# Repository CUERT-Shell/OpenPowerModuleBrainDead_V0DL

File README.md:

# OpenPowerModule

Kicad Design 
You can view on https://kicanvas.org (for non kicad users)

Minimal BLDC drive hardware (without microcontroller)

### The hardware 
* 3phase H-bridge and all its related circuitry (MGD , Snubber , decoupling , etc)
* Hall Sensor Conditioning Circuits
* IDC-2x15 Connector to be interfaced with a controller/MCU
* 12V-->5V buck converter , 3.3V LDO

### Repo Structure
* Main directory : design files
* Production directory : Gerbers and Bom
* LIB : Project Components library
* Doc : Design Reference , guide , step file , etc...

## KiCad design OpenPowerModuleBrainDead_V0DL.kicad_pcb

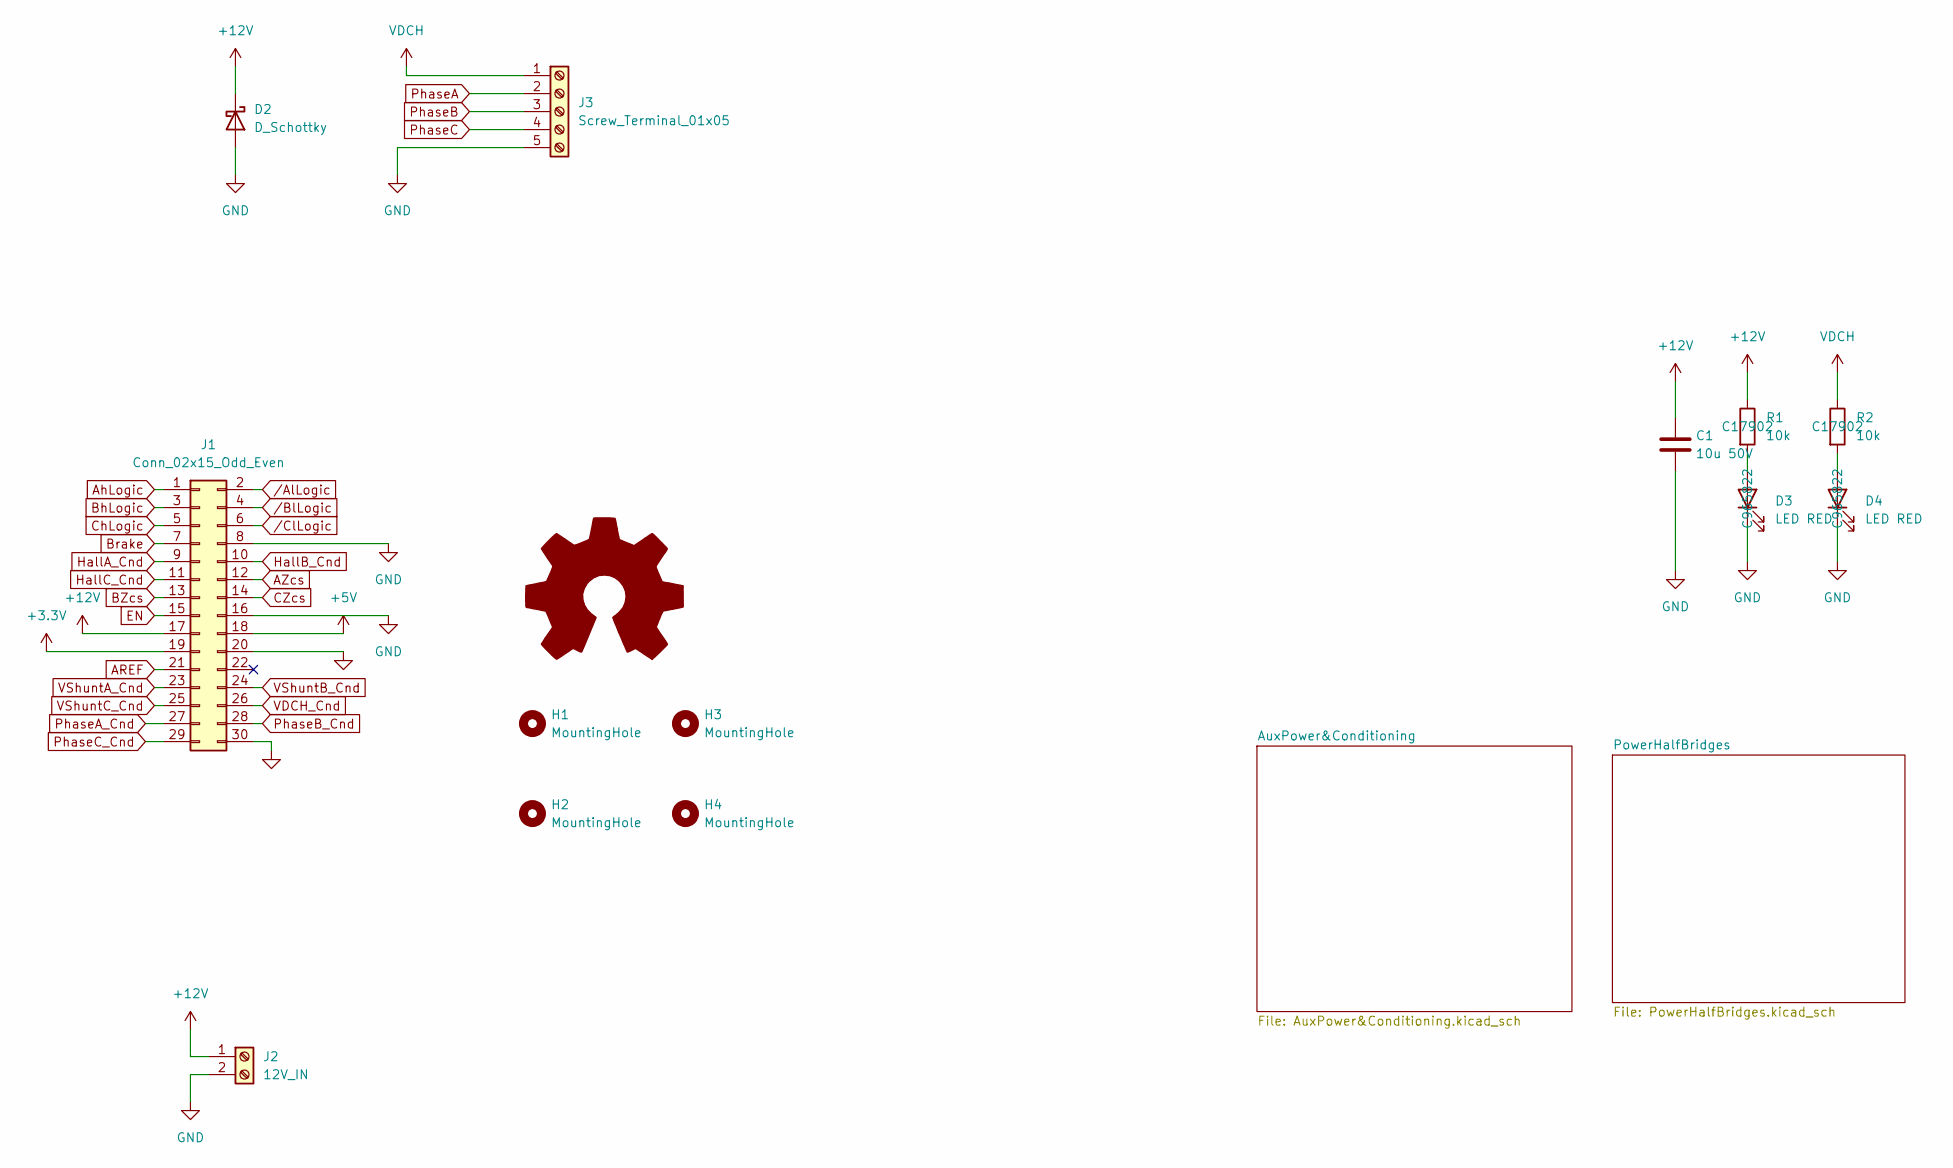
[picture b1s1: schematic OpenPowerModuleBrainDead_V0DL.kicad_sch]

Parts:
C1: 10u 50V; C_1206_3216Metric; LCSC Part C13585
D2: D_Schottky; D_SMC-RM10_Universal_Handsoldering
D3, D4: LED RED; LED_1206_3216Metric_Pad1.42x1.75mm_HandSolder; LCSC Part C965822
H1, H2, H3, H4: MountingHole; MountingHole_3.2mm_M3_DIN965
H5: Logo_Open_Hardware_Large; MadeWithKicad
J1: Conn_02x15_Odd_Even; IDC-Header_2x15_P2.54mm_Vertical
J2: 12V_IN; TerminalBlock_Phoenix_PT-1,5-2-3.5-H_1x02_P3.50mm_Horizontal
J3: Screw_Terminal_01x05; PowerConn_01x05_P20
R1, R2: 10k; R_1206_3216Metric; LCSC Part C17902

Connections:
+3.3V: J1.19; also elsewhere on the board
+5V: J1.18; also elsewhere on the board
+12V: C1.1, D2.1 (K), J1.17, J2.1, R1.1; also elsewhere on the board
AREF: J1.21
AZcs: J1.12
AhLogic: J1.1; also elsewhere on the board
BZcs: J1.13
BhLogic: J1.3; also elsewhere on the board
Brake: J1.7
CZcs: J1.14
ChLogic: J1.5; also elsewhere on the board
EN: J1.15
GND: C1.2, D2.2 (A), D3.1 (K), D4.1 (K), J1.8, J1.16, J1.20, J1.30, J2.2, J3.5; also elsewhere on the board
HallA_Cnd: J1.9; also elsewhere on the board
HallB_Cnd: J1.10; also elsewhere on the board
HallC_Cnd: J1.11; also elsewhere on the board
unnamed: D3.2 (A), R1.2
unnamed: D4.2 (A), R2.2
PhaseA: J3.2; also elsewhere on the board
PhaseA_Cnd: J1.27
PhaseB: J3.3; also elsewhere on the board
PhaseB_Cnd: J1.28
PhaseC: J3.4; also elsewhere on the board
PhaseC_Cnd: J1.29
VDCH: J3.1, R2.1; also elsewhere on the board
VDCH_Cnd: J1.26
VShuntA_Cnd: J1.23
VShuntB_Cnd: J1.24
VShuntC_Cnd: J1.25
/AlLogic: J1.2; also elsewhere on the board
/BlLogic: J1.4; also elsewhere on the board
/ClLogic: J1.6; also elsewhere on the board

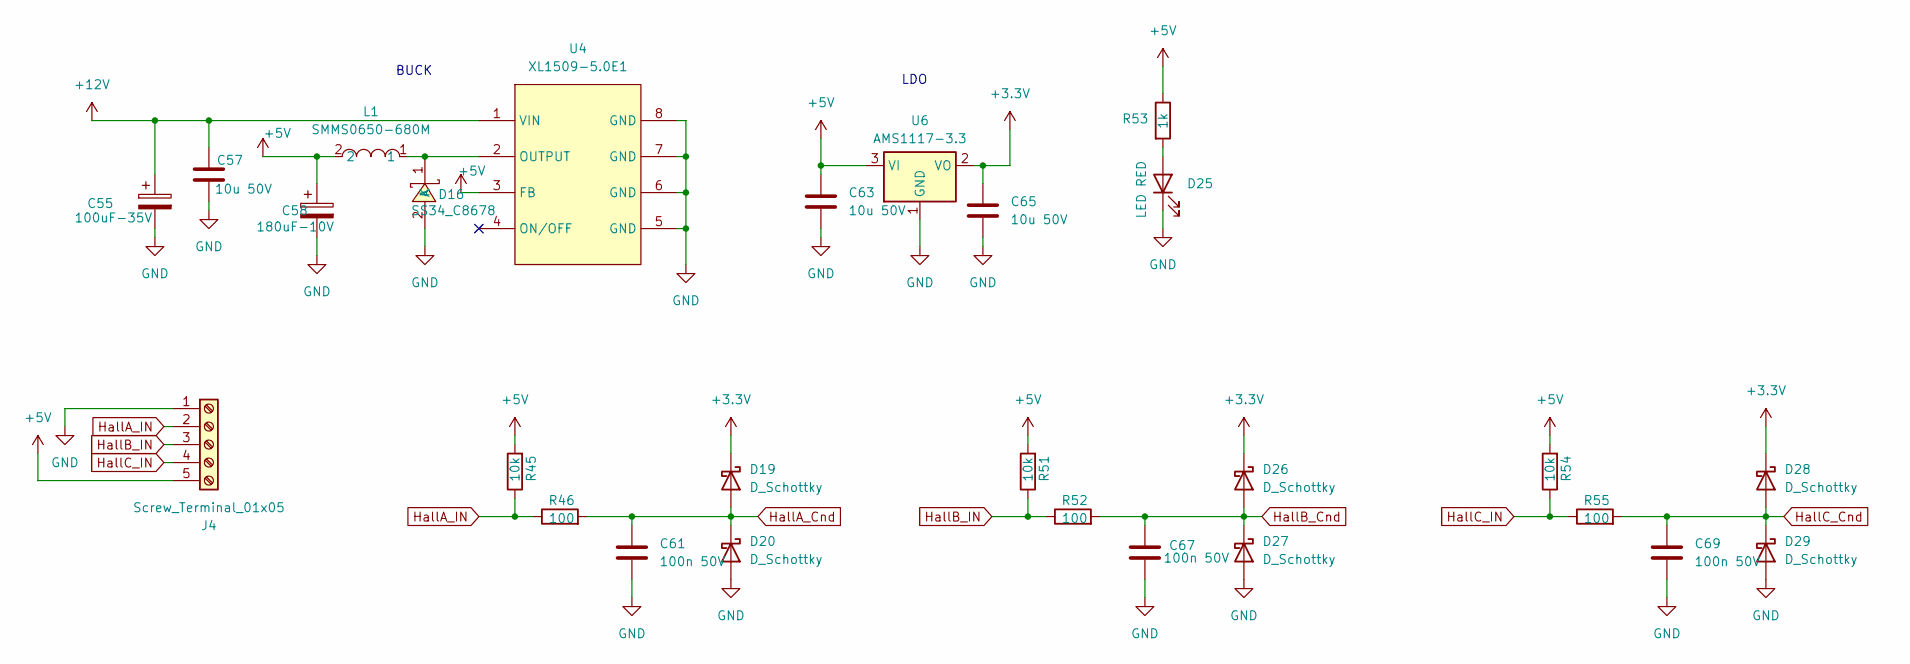
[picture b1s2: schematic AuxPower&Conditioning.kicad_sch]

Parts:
C55: 100uF-35V; CP_Radial_D6.3mm_P2.50mm
C57, C63, C65: 10u 50V; C_1206_3216Metric; LCSC Part C13585
C58: 180uF-10V; CP_Radial_D6.3mm_P2.50mm
C61, C67, C69: 100n 50V; C_1206_3216Metric; LCSC Part C24497
D16: SS34_C8678; SMA_L4.3-W2.6-LS5.2-RD; LCSC Part C8678
D19, D20, D26, D27, D28, D29: D_Schottky; D_SOD-123; LCSC Part C181204
D25: LED RED; LED_1206_3216Metric_Pad1.42x1.75mm_HandSolder; LCSC Part C965822
J4: Screw_Terminal_01x05; CONN-TH_5P-P3.50_DORABO_DB125-3.5-5P-GN-S
L1: SMMS0650-680M; IND-SMD_L7.1-W6.6_H5.0; LCSC Part C2894721
R45, R51, R54: 10k; R_1206_3216Metric; LCSC Part C17902
R46, R52, R55: 100; R_1206_3216Metric; LCSC Part C113307
R53: 1k; R_1206_3216Metric; LCSC Part C2907440
U4: XL1509-5.0E1; SOIC-8_L5.0-W4.0-P1.27-LS6.0-BL; LCSC Part C61063
U6: AMS1117-3.3; SOT-223-3_TabPin2; LCSC Part C347222

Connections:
+3.3V: C65.1, D19.1 (K), D26.1 (K), D28.1 (K), U6.2 (VO); also elsewhere on the board
+5V: C58.1, C63.1, J4.5, L1.2, R45.2, R51.2, R53.1, R54.2, U4.3 (FB), U6.3 (VI); also elsewhere on the board
+12V: C55.1, C57.1, U4.1 (VIN); also elsewhere on the board
GND: C55.2, C57.2, C58.2, C61.2, C63.2, C65.2, C67.2, C69.2, D16.2 (A), D20.2 (A), D25.1 (K), D27.2 (A), D29.2 (A), J4.1, U4.5 (GND), U4.6 (GND), U4.7 (GND), U4.8 (GND), U6.1 (GND); also elsewhere on the board
HallA_Cnd: C61.1, D19.2 (A), D20.1 (K), R46.2; also elsewhere on the board
HallA_IN: J4.2, R45.1, R46.1
HallB_Cnd: C67.1, D26.2 (A), D27.1 (K), R52.2; also elsewhere on the board
HallB_IN: J4.3, R51.1, R52.1
HallC_Cnd: C69.1, D28.2 (A), D29.1 (K), R55.2; also elsewhere on the board
HallC_IN: J4.4, R54.1, R55.1
unnamed: D16.1 (K), L1.1, U4.2 (OUTPUT)
unnamed: D25.2 (A), R53.2

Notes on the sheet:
LDO
BUCK

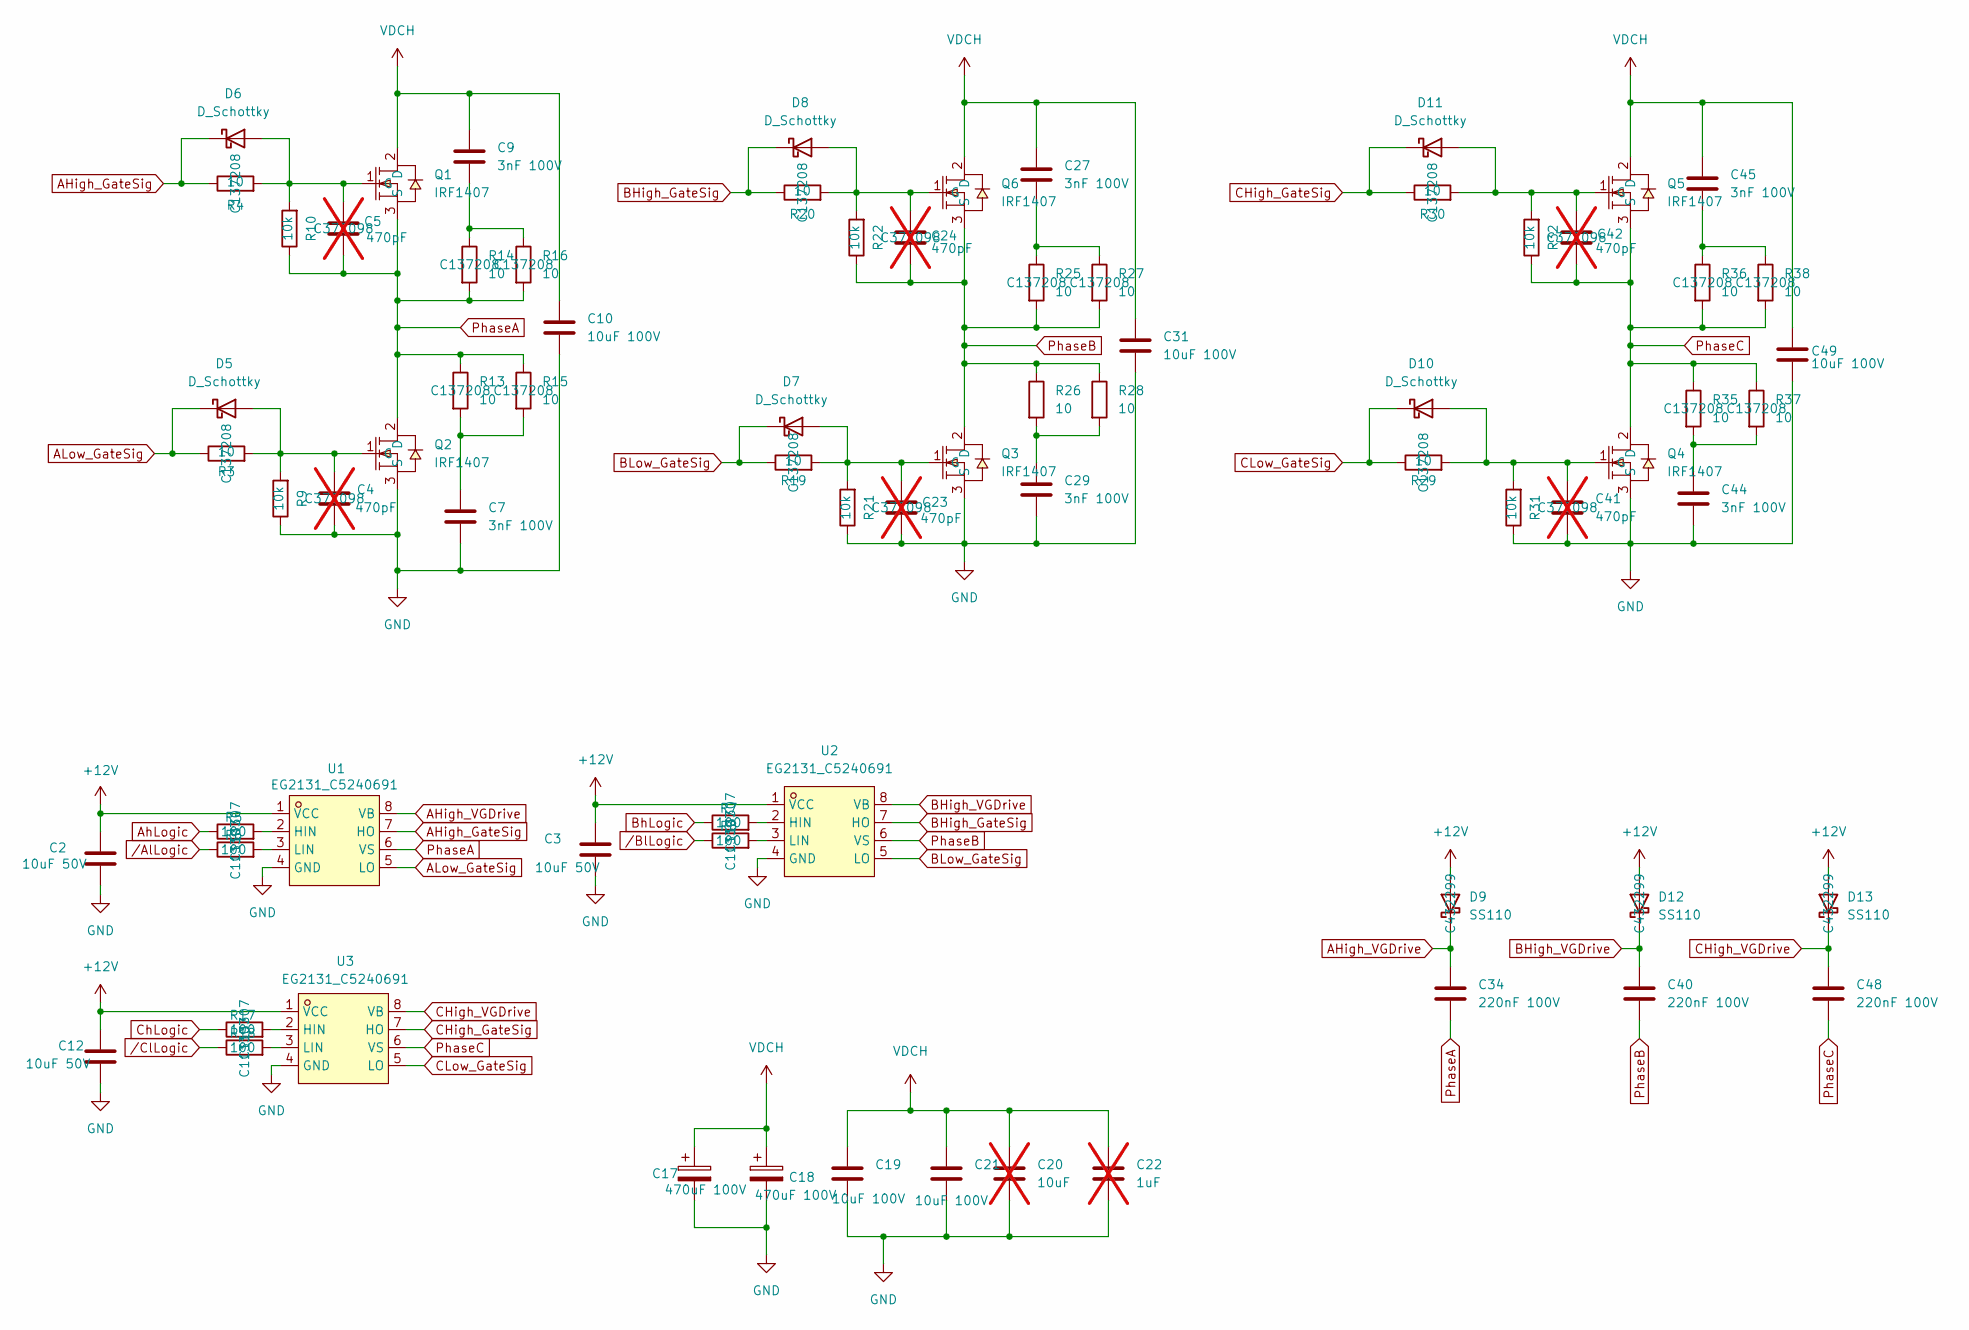
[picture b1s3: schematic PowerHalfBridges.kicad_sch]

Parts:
C2, C3, C12: 10uF 50V; C_1206_3216Metric; LCSC Part C7432781
C4, C5, C23, C24, C41, C42: 470pF; C_1206_3216Metric; LCSC Part C377098; not fitted
C7, C9, C27, C29, C44, C45: 3nF 100V; C_1206_3216Metric; LCSC Part C7393993
C10, C19, C21, C31, C49: 10uF 100V; C_1210_3225Metric; LCSC Part C5156756
C17, C18: 470uF 100V; CP_Radial_D16.0mm_P7.50mm
C20: 10uF; C_Rect_L18.0mm_W7.0mm_P15.00mm_FKS3_FKP3; not fitted
C22: 1uF; C_Rect_L18.0mm_W7.0mm_P15.00mm_FKS3_FKP3; not fitted
C34, C40, C48: 220nF 100V; C_1206_3216Metric; LCSC Part C377088
D5, D6, D7, D8, D10, D11: D_Schottky; D_SOD-123; LCSC Part C181204
D9, D12, D13: SS110; D_SMA; LCSC Part C432299
Q1, Q2, Q3, Q4, Q5, Q6: IRF1407; TO-220-3_Horizontal_TabUp; LCSC Part C33129604
R3, R4, R13, R14, R15, R16, R19, R20, R25, R26, R27, R28, R29, R30, R35, R36, R37, R38: 10; R_1206_3216Metric; LCSC Part C137208
R5, R6, R7, R8, R17, R18: 100; R_1206_3216Metric; LCSC Part C113307
R9, R10, R21, R22, R31, R32: 10k; R_1206_3216Metric; LCSC Part C17902
U1, U2, U3: EG2131_C5240691; SOP-8_L4.9-W3.9-P1.27-LS6.0-BL; LCSC Part C5240691

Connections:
+12V: C2.1, C3.1, C12.1, D9.2 (A), D12.2 (A), D13.2 (A), U1.1 (VCC), U2.1 (VCC), U3.1 (VCC); also elsewhere on the board
AHigh_GateSig: D6.1 (K), R4.1, U1.7 (HO)
AHigh_VGDrive: C34.1, D9.1 (K), U1.8 (VB)
ALow_GateSig: D5.1 (K), R3.1, U1.5 (LO)
AhLogic: R5.1; also elsewhere on the board
BHigh_GateSig: D8.1 (K), R20.1, U2.7 (HO)
BHigh_VGDrive: C40.1, D12.1 (K), U2.8 (VB)
BLow_GateSig: D7.1 (K), R19.1, U2.5 (LO)
BhLogic: R7.1; also elsewhere on the board
CHigh_GateSig: D11.1 (K), R30.1, U3.7 (HO)
CHigh_VGDrive: C48.1, D13.1 (K), U3.8 (VB)
CLow_GateSig: D10.1 (K), R29.1, U3.5 (LO)
ChLogic: R17.1; also elsewhere on the board
GND: C2.2, C3.2, C4.2, C7.2, C10.2, C12.2, C17.2, C18.2, C19.2, C20.2, C21.2, C22.2, C23.2, C29.2, C31.2, C41.2, C44.2, C49.2, Q2.3 (S), Q3.3 (S), Q4.3 (S), R9.1, R21.1, R31.1, U1.4 (GND), U2.4 (GND), U3.4 (GND); also elsewhere on the board
unnamed: C7.1, R13.2, R15.2
unnamed: C9.2, R14.1, R16.1
unnamed: C27.2, R25.1, R27.1
unnamed: C29.1, R26.2, R28.2
unnamed: C44.1, R35.2, R37.2
unnamed: C45.2, R36.1, R38.1
unnamed: C4.1, D5.2 (A), Q2.1 (G), R3.2, R9.2
unnamed: C5.1, D6.2 (A), Q1.1 (G), R4.2, R10.2
unnamed: C23.1, D7.2 (A), Q3.1 (G), R19.2, R21.2
unnamed: C24.1, D8.2 (A), Q6.1 (G), R20.2, R22.2
unnamed: C41.1, D10.2 (A), Q4.1 (G), R29.2, R31.2
unnamed: C42.1, D11.2 (A), Q5.1 (G), R30.2, R32.2
unnamed: R5.2, U1.2 (HIN)
unnamed: R6.2, U1.3 (LIN)
unnamed: R7.2, U2.2 (HIN)
unnamed: R8.2, U2.3 (LIN)
unnamed: R17.2, U3.2 (HIN)
unnamed: R18.2, U3.3 (LIN)
PhaseA: C5.2, C34.2, Q1.3 (S), Q2.2 (D), R10.1, R13.1, R14.2, R15.1, R16.2, U1.6 (VS); also elsewhere on the board
PhaseB: C24.2, C40.2, Q3.2 (D), Q6.3 (S), R22.1, R25.2, R26.1, R27.2, R28.1, U2.6 (VS); also elsewhere on the board
PhaseC: C42.2, C48.2, Q4.2 (D), Q5.3 (S), R32.1, R35.1, R36.2, R37.1, R38.2, U3.6 (VS); also elsewhere on the board
VDCH: C9.1, C10.1, C17.1, C18.1, C19.1, C20.1, C21.1, C22.1, C27.1, C31.1, C45.1, C49.1, Q1.2 (D), Q5.2 (D), Q6.2 (D); also elsewhere on the board
/AlLogic: R6.1; also elsewhere on the board
/BlLogic: R8.1; also elsewhere on the board
/ClLogic: R18.1; also elsewhere on the board

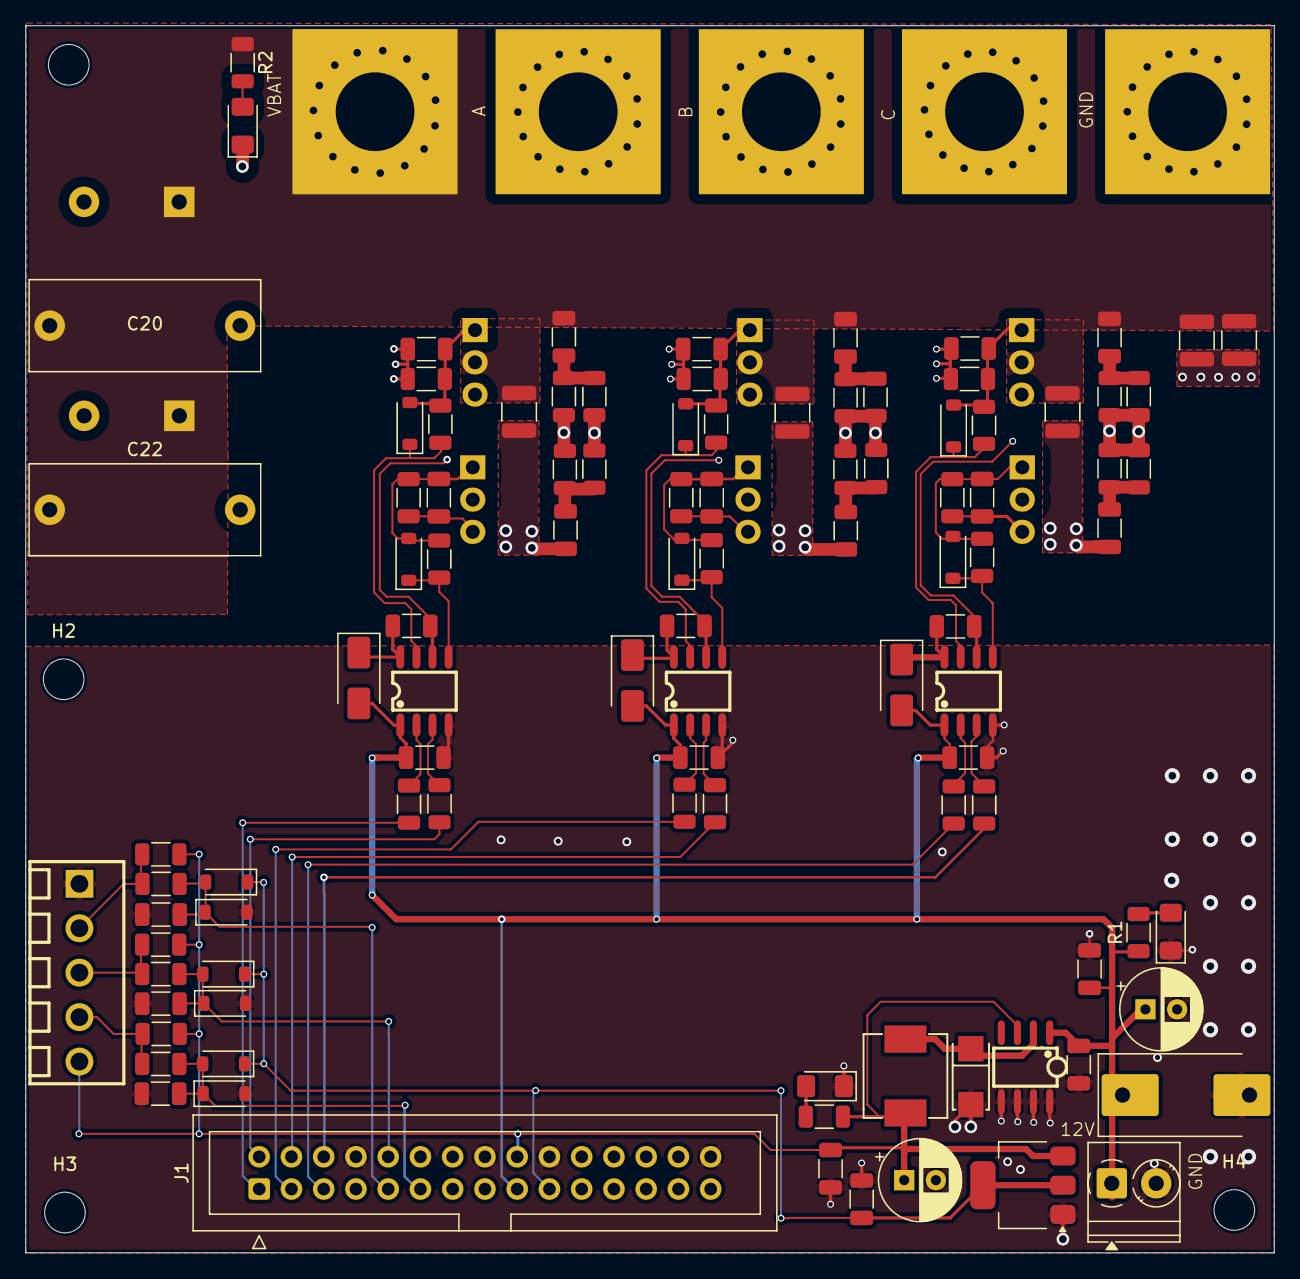
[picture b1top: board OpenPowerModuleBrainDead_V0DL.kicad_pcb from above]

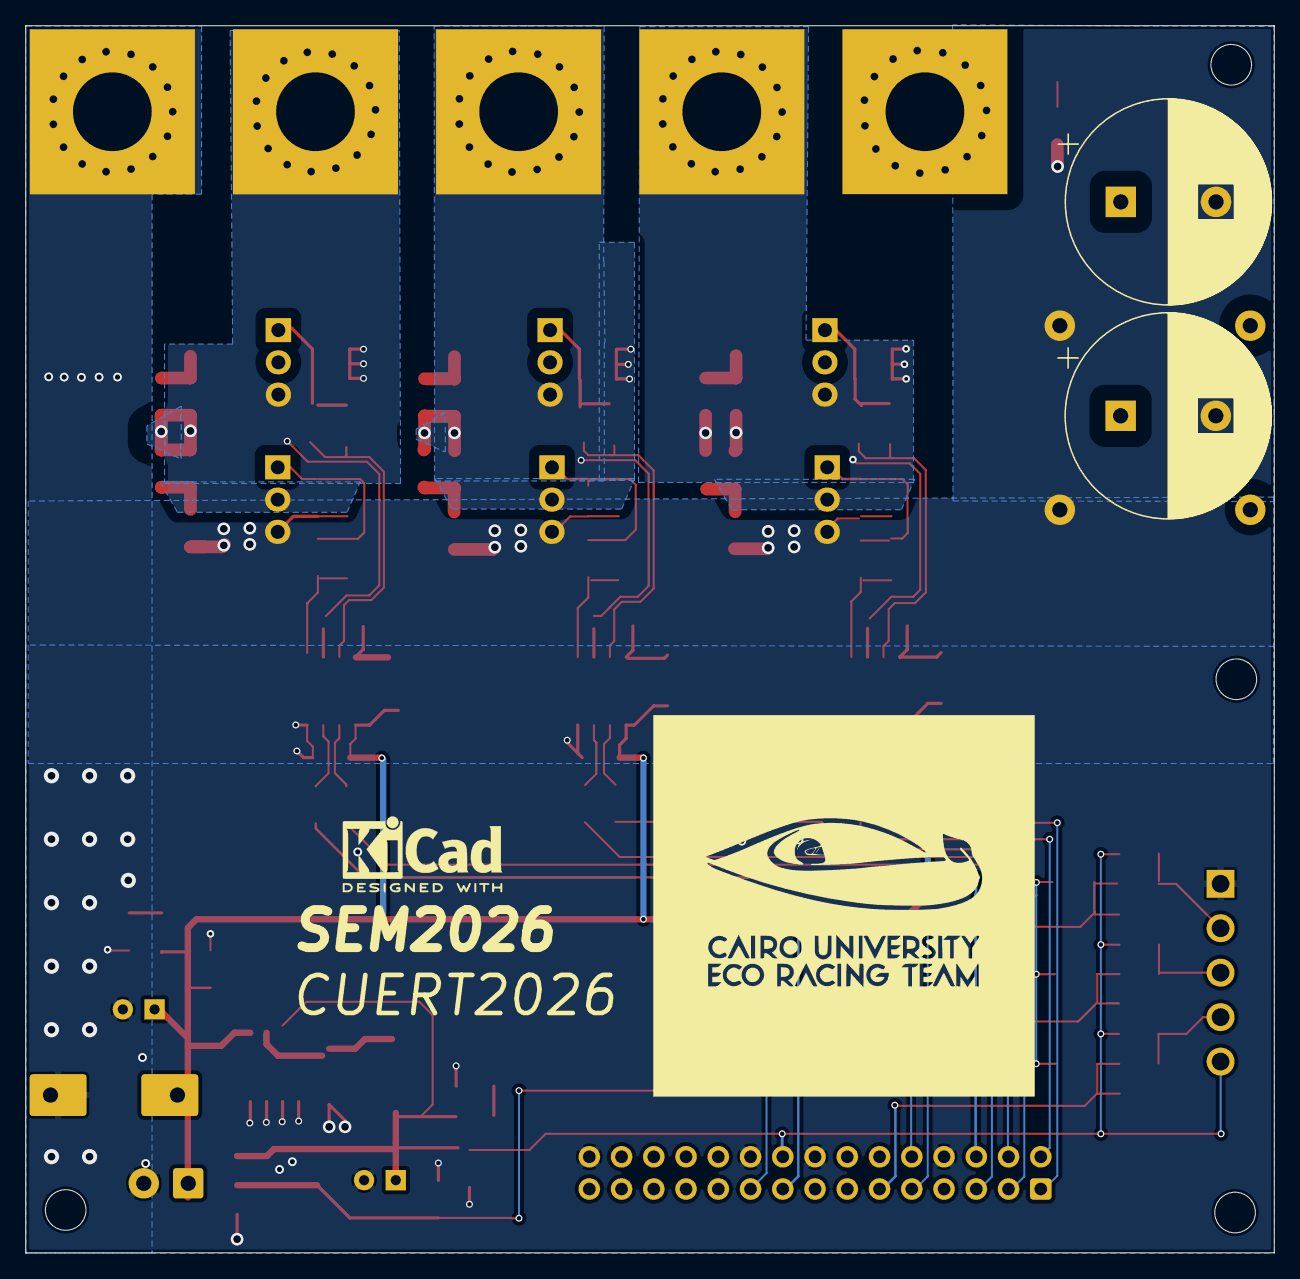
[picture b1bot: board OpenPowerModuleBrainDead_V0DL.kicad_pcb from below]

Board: 2 copper layers, 98.3 x 96.6 mm, 116 parts (9 on the bottom side), 51 nets.

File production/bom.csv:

Designator,Footprint,Quantity,Value,LCSC Part #
"C1, C57, C63, C65",1206,4,10u 50V,C13585
"C10, C19, C21, C31, C49",1210,5,10uF 100V,C5156756
"C12, C2, C3",1206,3,10uF 50V,C7432781
"C23, C24, C4, C41, C42, C5",1206,6,470pF,C377098
"C27, C29, C44, C45, C7, C9",1206,6,3nF 100V,C7393993
"C34, C40, C48",1206,3,220nF 100V,C377088
"C61, C67, C69",1206,3,100n 50V,C24497
"D10, D11, D19, D20, D26, D27, D28, D29, D5, D6, D7, D8",D_SOD-123,12,D_Schottky,C181204
"D12, D13, D9",D_SMA,3,SS110,C432299
D16,SMA_L4.3-W2.6-LS5.2-RD,1,SS34_C8678,C8678
"D25, D3, D4",1206,3,LED RED,C965822
L1,IND-SMD_L7.1-W6.6_H5.0,1,SMMS0650-680M,C2894721
"Q1, Q2, Q3, Q4, Q5, Q6",TO-220-3_Horizontal_TabUp,6,IRF1407,C33129604
"R1, R10, R2, R21, R22, R31, R32, R45, R51, R54, R9",1206,11,10k,C17902
"R13, R14, R15, R16, R19, R20, R25, R26, R27, R28, R29, R3, R30, R35, R36, R37, R38, R4",1206,18,10,C137208
"R17, R18, R46, R5, R52, R55, R6, R7, R8",1206,9,100,C113307
R53,1206,1,1k,C2907440
"U1, U2, U3",SOP-8_L4.9-W3.9-P1.27-LS6.0-BL,3,EG2131_C5240691,C5240691
U4,SOIC-8_L5.0-W4.0-P1.27-LS6.0-BL,1,XL1509-5.0E1,C61063
U6,SOT-223-3_TabPin2,1,AMS1117-3.3,C347222

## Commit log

2025-09-22 Init
2025-09-22 Brief Documentation
